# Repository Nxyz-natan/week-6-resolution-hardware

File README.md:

# RP2350A IMU Dev Board

A custom dev board built around the RP2350A microcontroller with an 
onboard MPU-6050 IMU for motion sensing, housed in a custom 3D printed case.

PCB Render:

## How it works

The board uses a USB-C connector and an AMS1117-33 LDO to regulate 
5V down to 3.3V. The RP2350A runs with a 12MHz crystal oscillator and 
W25Q128 flash memory over QSPI. The MPU-6050 IMU connects over I2C on 
GPIO4 and GPIO5 for motion sensing. GPIO headers expose the remaining 
pins for external use.

KiCanvas Link: https://kicanvas.org/?repo=https%3A%2F%2Fgithub.com%2FNxyz-natan%2Fweek-7-and-8-resolution-hardware%2Ftree%2Fmain%2Fsrc%2Fkicad

Case Design Link: https://app.shapr3d.com/p/ce0b803e-1716-4454-bb49-c60d17f44aa6

## Schematic

Schematic: 

## PCB

PCB: 

## Case

Case: 

## Bill of Materials

| Ref | Value  LCSC # |
|-----|---------------|
| U1 | RP2350A | C42411118 |
| U2 | W25Q128JVSIQ | C97521 |
| U3 | AMS1117-3.3 | C6186 |
| U4 | MPU-6050 | C24112 |
| R1, R2 | 5.1k 0603 | C2907044 |
| R3 | 1k 0603 | C22548 |
| R4, R5 | 27Ω 0603 | C137753 |
| R6, R7 | 10k 0603 | TBD |
| R8, R9 | 4.7k 0603 | C99782 |
| C1-C4 | 1uF 0603 | C15849 |
| C5-C11, C14-C18 | 100nF 0603  | C14663 |
| C12, C13 | 15pF 0603 | C1644 |
| Y1 | 12MHz Crystal SMD3225 | C9002 |
| J1 | USB-C TYPE-C-31-M-12 | C165948 |
| J2 | 1x04 Pin Header 2.54mm | C52016392 |
| J4 | 1x20 Pin Header 2.54mm | C50981 |
| J5 | 1x13 Pin Header 2.54mm  | C42372505 |
| SW1, SW2 | SW Push 6x6mm | C318884 |

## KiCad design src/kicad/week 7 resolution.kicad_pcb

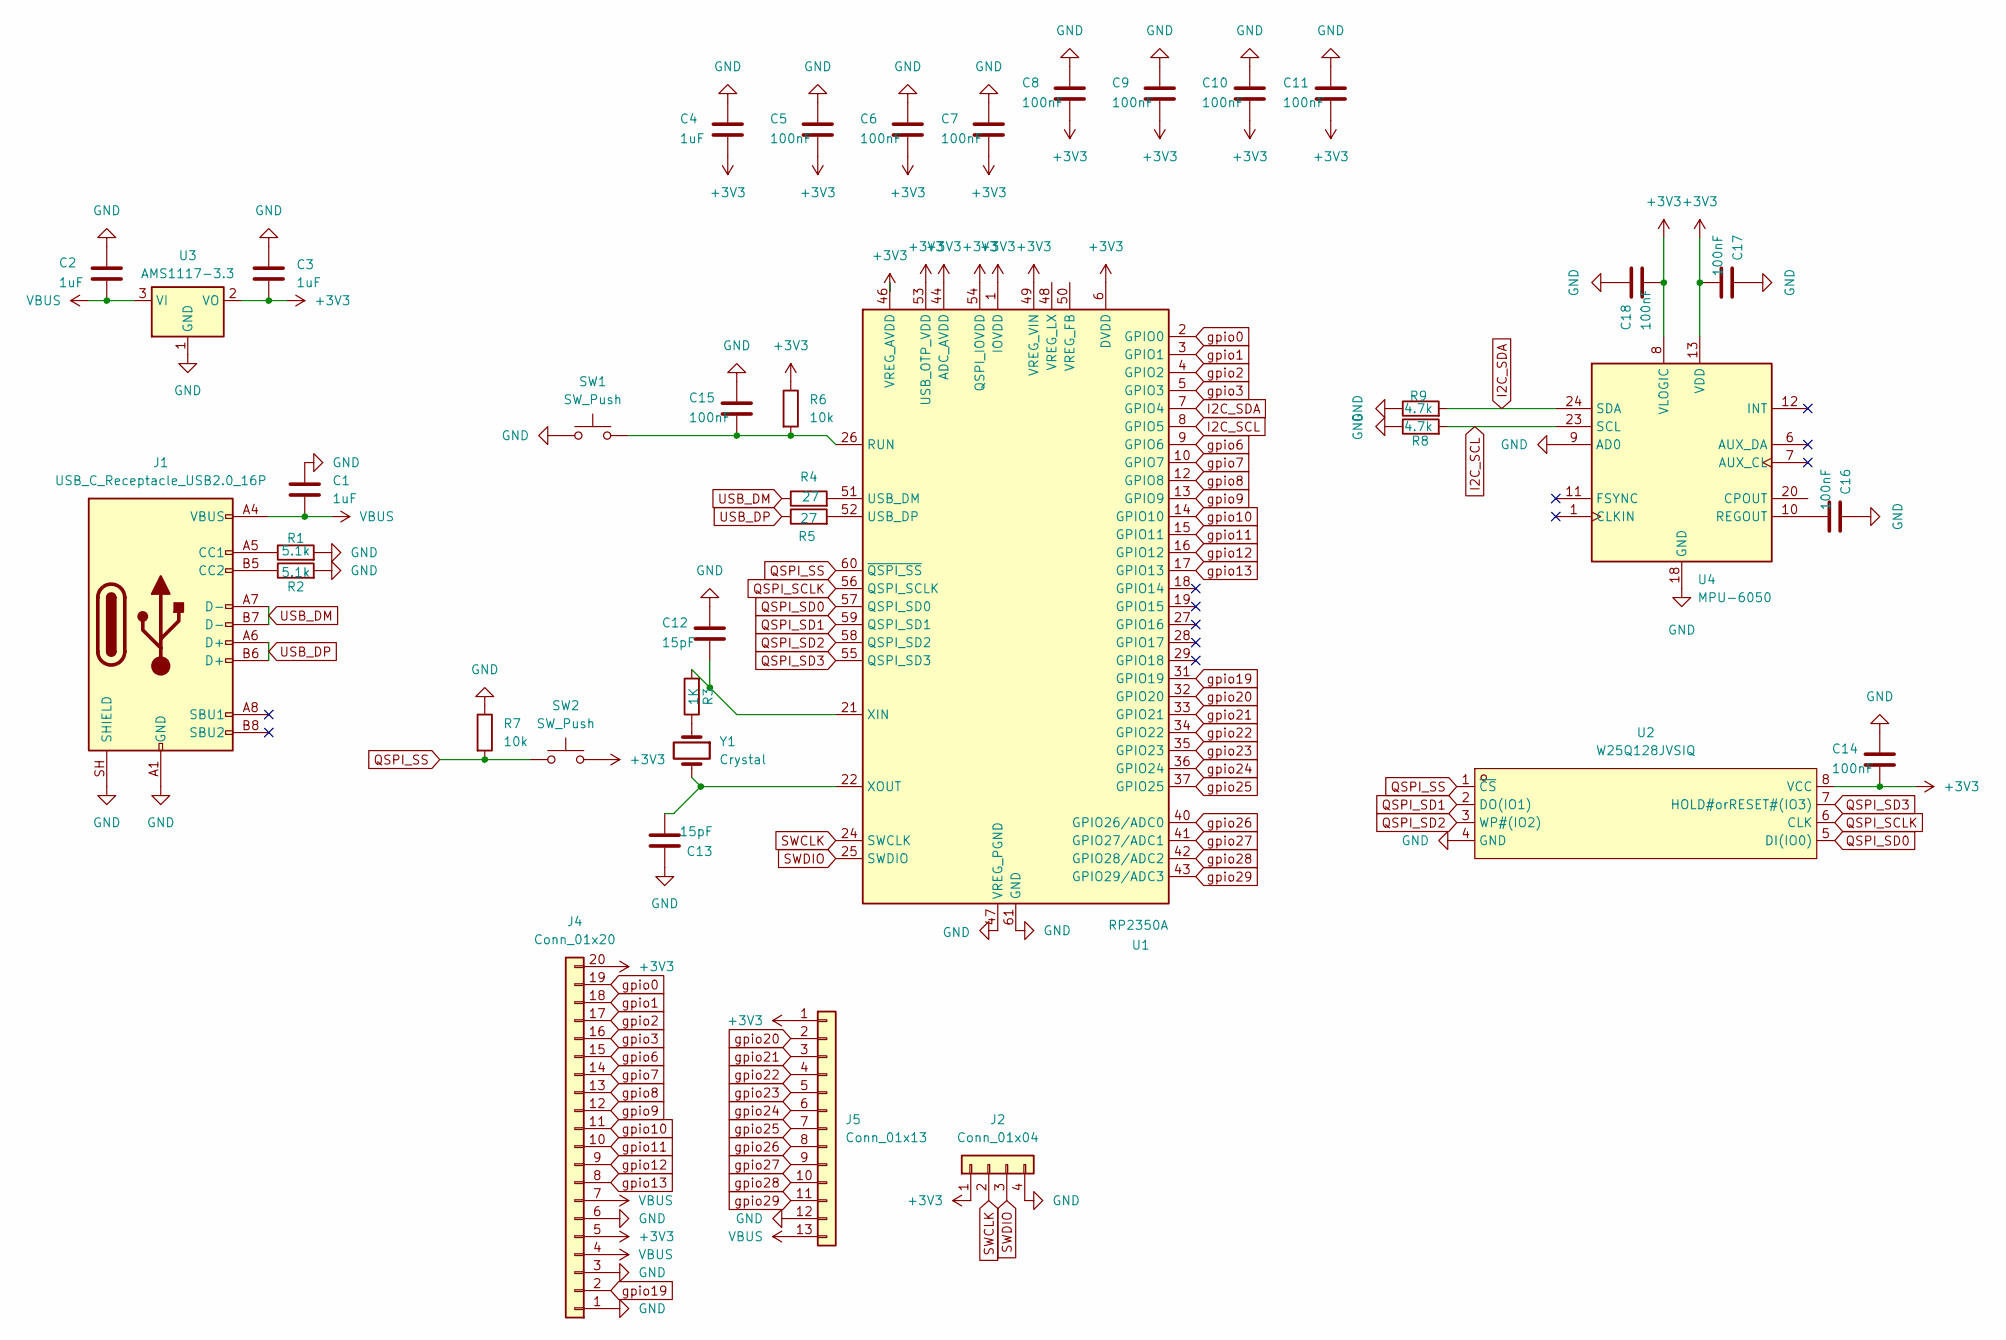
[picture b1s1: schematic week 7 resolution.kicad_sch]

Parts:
C1, C2, C3, C4: 1uF; C_0603_1608Metric
C5, C6, C7, C8, C9, C10, C11, C14, C15, C16, C17, C18: 100nF; C_0603_1608Metric
C12, C13: 15pF; C_0603_1608Metric
J1: USB_C_Receptacle_USB2.0_16P; USB_C_Receptacle_HRO_TYPE-C-31-M-12
J2: Conn_01x04; PinHeader_1x04_P2.54mm_Vertical
J4: Conn_01x20; PinHeader_1x20_P2.54mm_Vertical
J5: Conn_01x13; PinHeader_1x13_P2.54mm_Vertical
R1, R2: 5.1k; R_0603_1608Metric
R3: 1K; R_0603_1608Metric
R4, R5: 27; R_0603_1608Metric
R6, R7: 10k; R_0603_1608Metric
R8, R9: 4.7k; R_0603_1608Metric
SW1, SW2: SW_Push; SW_Push_1TS009xxxx-xxxx-xxxx_6x6x5mm
U1: RP2350A; QFN-60-1EP_7x7mm_P0.4mm_EP3.4x3.4mm
U2: W25Q128JVSIQ; SOIC-8_L5.3-W5.3-P1.27-LS8.0-BL; MPN W25Q128JVSIQ; LCSC Part C113767
U3: AMS1117-3.3; SOT-223-3_TabPin2
U4: MPU-6050; InvenSense_QFN-24_4x4mm_P0.5mm
Y1: Crystal; Crystal_SMD_3225-4Pin_3.2x2.5mm

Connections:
+3V3: C3.2, C4.2, C5.2, C6.2, C7.2, C8.2, C9.2, C10.2, C11.2, C14.2, C17.2, C18.2, J2.1, J4.5, J4.20, J5.1, R6.1, SW2.2, U1.1 (IOVDD), U1.6 (DVDD), U1.11 (IOVDD), U1.20 (IOVDD), U1.23 (DVDD), U1.30 (IOVDD), U1.38 (IOVDD), U1.39 (DVDD), U1.44 (ADC_AVDD), U1.45 (IOVDD), U1.46 (VREG_AVDD), U1.49 (VREG_VIN), U1.53 (USB_OTP_VDD), U1.54 (QSPI_IOVDD), U2.8 (VCC), U3.2 (VO), U4.8 (VLOGIC), U4.13 (VDD); also elsewhere on the board
GND: C1.1, C2.1, C3.1, C4.1, C5.1, C6.1, C7.1, C8.1, C9.1, C10.1, C11.1, C12.1, C13.1, C14.1, C15.1, C16.1, C17.1, C18.1, J1.A1 (GND), J1.A12 (GND), J1.B1 (GND), J1.B12 (GND), J1.SH (SHIELD), J2.4, J4.1, J4.3, J4.6, J5.12, R1.2, R2.2, R7.1, R8.1, R9.1, SW1.1, U1.47 (VREG_PGND), U1.61 (GND), U2.4 (GND), U3.1 (GND), U4.9 (AD0), U4.18 (GND); also elsewhere on the board
I2C_SCL: R8.2, U1.8 (GPIO5), U4.23 (SCL)
I2C_SDA: R9.2, U1.7 (GPIO4), U4.24 (SDA)
unnamed: J1.A5 (CC1), R1.1
unnamed: J1.B5 (CC2), R2.1
unnamed: R3.1, Y1.1
unnamed 7: C15.2, R6.2, SW1.2, U1.26 (RUN); also elsewhere on the board
unnamed: R4.2, U1.51 (USB_DM)
unnamed: R5.2, U1.52 (USB_DP)
unnamed: C16.2, U4.10 (REGOUT)
QSPI_SCLK: U1.56 (QSPI_SCLK), U2.6 (CLK)
QSPI_SD0: U1.57 (QSPI_SD0), U2.5 (DI(IO0))
QSPI_SD1: U1.59 (QSPI_SD1), U2.2 (DO(IO1))
QSPI_SD2: U1.58 (QSPI_SD2), U2.3 (WP#(IO2))
QSPI_SD3: U1.55 (QSPI_SD3), U2.7 (HOLD#orRESET#(IO3))
QSPI_SS: R7.2, SW2.1, U1.60 (~QSPI_SS), U2.1 (~CS); also elsewhere on the board
SWCLK: J2.2, U1.24 (SWCLK)
SWDIO: J2.3, U1.25 (SWDIO)
USB_DM: J1.A7 (D-), J1.B7 (D-), R4.1
USB_DP: J1.A6 (D+), J1.B6 (D+), R5.1
VBUS: C1.2, C2.2, J1.A4 (VBUS), J1.A9 (VBUS), J1.B4 (VBUS), J1.B9 (VBUS), J4.4, J4.7, J5.13, U3.3 (VI)
gpio0: J4.19, U1.2 (GPIO0)
gpio1: J4.18, U1.3 (GPIO1)
gpio2: J4.17, U1.4 (GPIO2)
gpio3: J4.16, U1.5 (GPIO3)
gpio6: J4.15, U1.9 (GPIO6)
gpio7: J4.14, U1.10 (GPIO7)
gpio8: J4.13, U1.12 (GPIO8)
gpio9: J4.12, U1.13 (GPIO9)
gpio10: J4.11, U1.14 (GPIO10)
gpio11: J4.10, U1.15 (GPIO11)
gpio12: J4.9, U1.16 (GPIO12)
gpio13: J4.8, U1.17 (GPIO13)
gpio19: J4.2, U1.31 (GPIO19)
gpio20: J5.2, U1.32 (GPIO20)
gpio21: J5.3, U1.33 (GPIO21)
gpio22: J5.4, U1.34 (GPIO22)
gpio23: J5.5, U1.35 (GPIO23)
gpio24: J5.6, U1.36 (GPIO24)
gpio25: J5.7, U1.37 (GPIO25)
gpio26: J5.8, U1.40 (GPIO26/ADC0)
gpio27: J5.9, U1.41 (GPIO27/ADC1)
gpio28: J5.10, U1.42 (GPIO28/ADC2)
gpio29: J5.11, U1.43 (GPIO29/ADC3)
xin: C12.2, R3.2, U1.21 (XIN)
xout: C13.2, U1.22 (XOUT), Y1.2

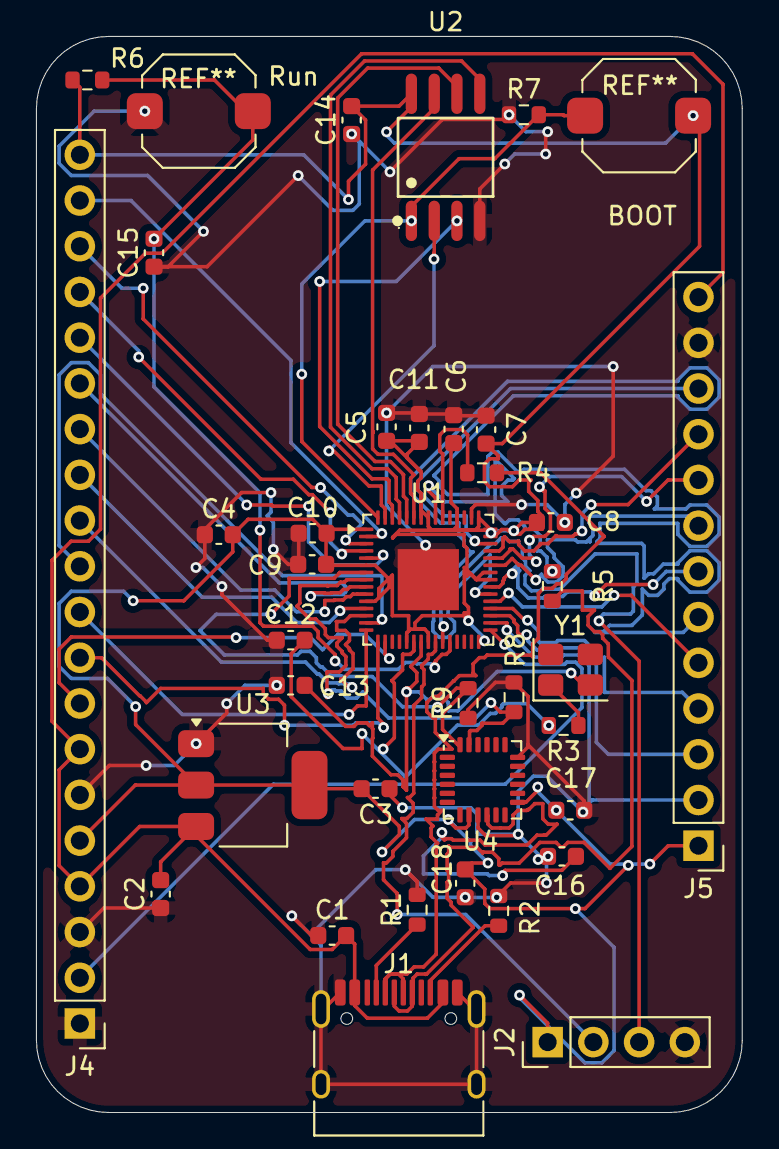
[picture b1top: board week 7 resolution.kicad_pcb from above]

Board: 2 copper layers, 39.2 x 59.8 mm, 38 parts (0 on the bottom side), 47 nets.

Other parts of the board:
BOOT: SW_Push; SW_Push_1TS009xxxx-xxxx-xxxx_6x6x5mm
Run: SW_Push; SW_Push_1TS009xxxx-xxxx-xxxx_6x6x5mm

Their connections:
+3V3: BOOT.2; also elsewhere on the board
GND: Run.1; also elsewhere on the board
unnamed 7: Run.2; also elsewhere on the board
QSPI_SS: BOOT.1; also elsewhere on the board

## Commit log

2026-05-28 Fix image links and add details on PCB design
    Updated README.md with corrected image links and additional details about the PCB design and USB-C wiring issues.
2026-05-30 Rename week 6/week 6 resolution.kicad_pcb to src/kicad/week 7 resolution.kicad_pcb
2026-05-30 Rename week 6/week 6 resolution.kicad_pro to src/kicad/week 7 resolution.kicad_pro
2026-05-30 Add week 7 resolution schematic file
2026-05-30 Rename Archive.zip to Gerbers.zip
2026-05-30 update BOM format
2026-05-30 Rename devboard case.stl to devboard case.stl
2026-05-30 Rename devboard top.stl to devboard top.stl
